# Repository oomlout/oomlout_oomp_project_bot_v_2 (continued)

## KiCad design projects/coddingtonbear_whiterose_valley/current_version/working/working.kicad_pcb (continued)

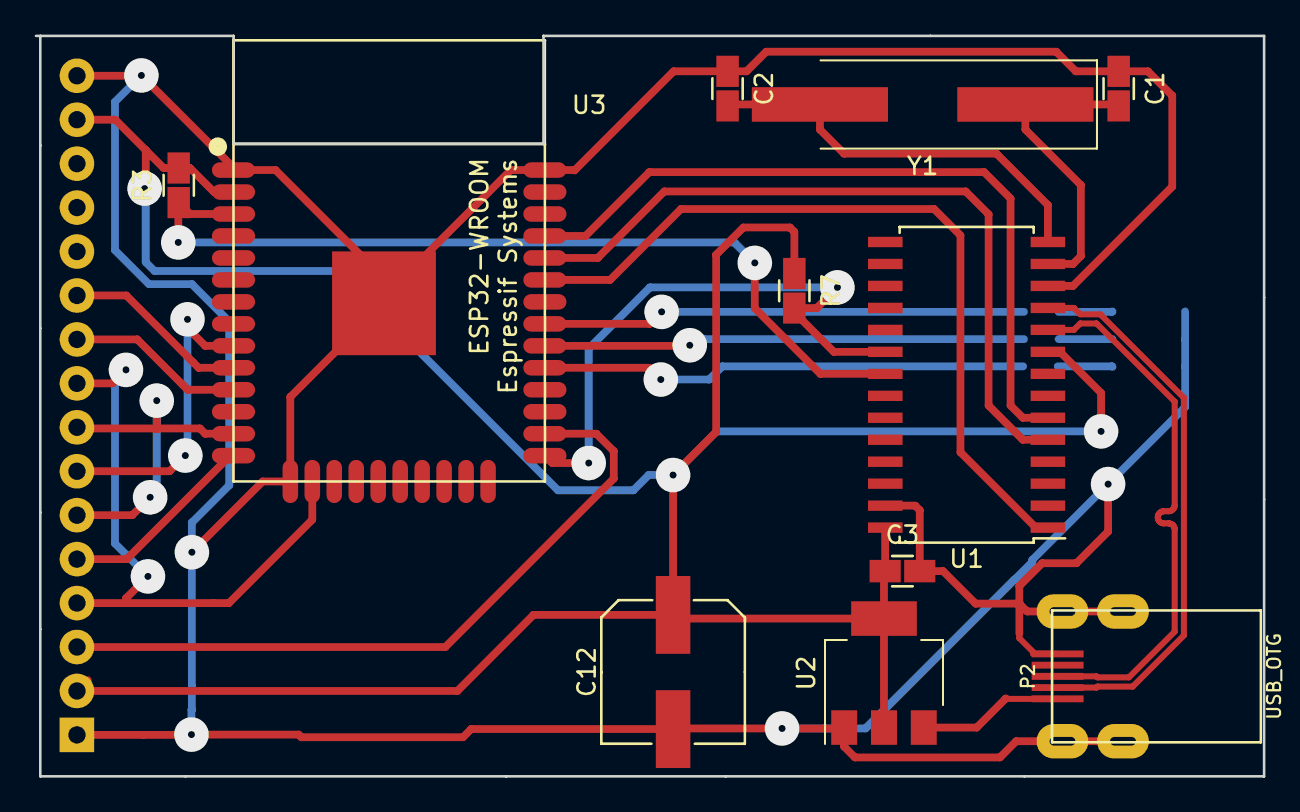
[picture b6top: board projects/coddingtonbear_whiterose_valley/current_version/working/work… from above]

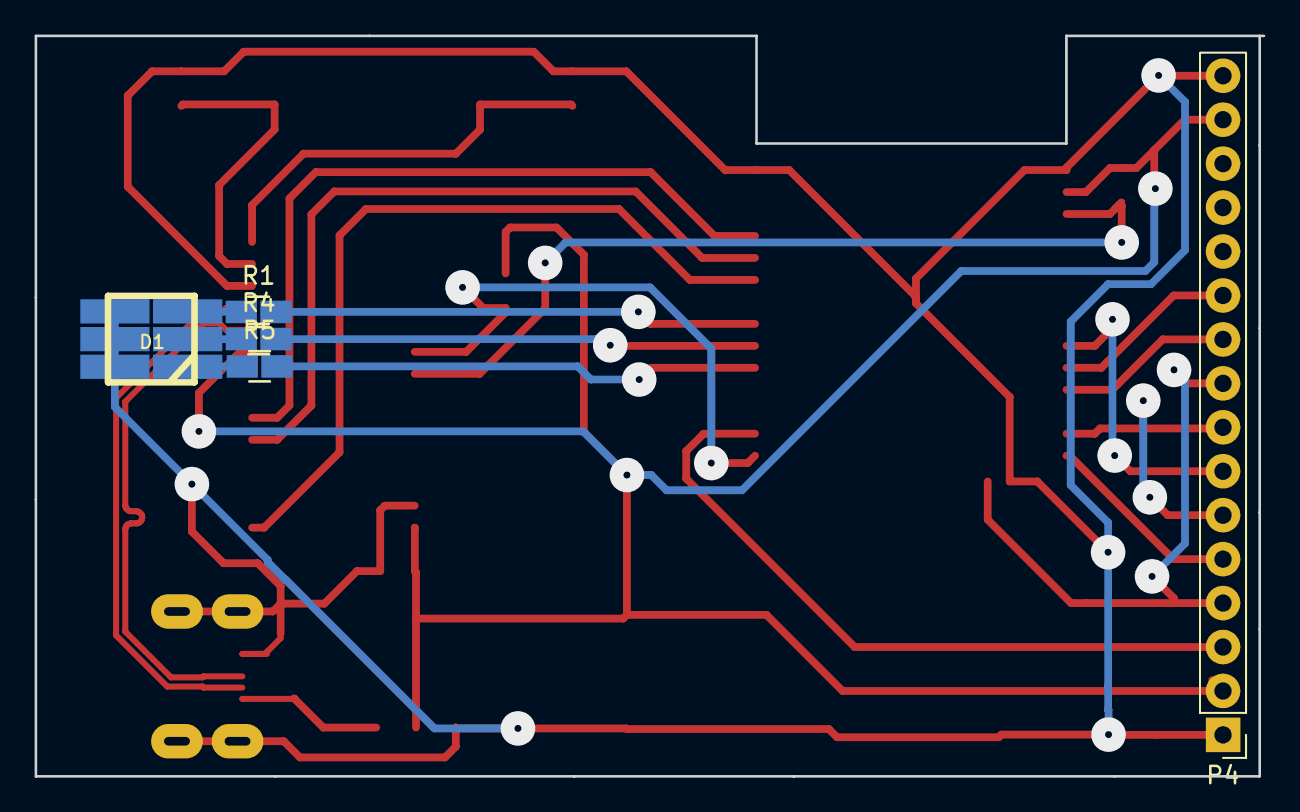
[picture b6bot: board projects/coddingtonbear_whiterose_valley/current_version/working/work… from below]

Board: 2 copper layers, 71.0 x 42.8 mm, 16 parts (5 on the bottom side), 25 nets.

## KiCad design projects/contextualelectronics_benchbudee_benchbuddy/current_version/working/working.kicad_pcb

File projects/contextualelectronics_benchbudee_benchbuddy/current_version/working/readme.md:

# benchbudee
 
## summary 
* id: contextualelectronics_benchbudee_benchbuddy
* user: contextualelectronics
* name: benchbudee
* board: benchbuddy
* repo: https://github.com/ContextualElectronics/BenchBudEE
* src_file_repo_kicad_pcb: BenchBuddy.kicad_pcb
* src_file_repo_kicad_pcb_link: https://github.com/ContextualElectronics/BenchBudEE/tree/master/BenchBuddy.kicad_pcb

* src_file_repo_sch: 
* src_file_repo_sch_link: https://github.com/ContextualElectronics/BenchBudEE/tree/master/
* full details link: https://github.com/oomlout/oomlout_oomp_project_bot_v_2/tree/main/projects/contextualelectronics_benchbudee_benchbuddy/current_version/working  

## schematic  
  
[schematic (pdf)](working_schematic.pdf) 

## pcb  

[board (pdf)](working.pdf)  

## working_bom
| Id | Designator | Footprint | Quantity | Designation | Supplier and ref |  | None | 
| --- | --- | --- | --- | --- | --- | --- | --- | 
| 1 | D2,D4 | SMA | 2 | B130-13-F |  |  | [''] | 
| 2 | R5,R3,R48,R49,R62,R63,R6,R58,R61 | SM0805 | 9 | 0 |  |  | [''] | 
| 3 | R2 | SM0805 | 1 | 200 |  |  | [''] | 
| 4 | U1 | 4-SMD | 1 | LTV-816S |  |  | [''] | 
| 5 | U2 | SSOP20 | 1 | MCP3901 |  |  | [''] | 
| 6 | U4 | SO14N | 1 | OPA4170 |  |  | [''] | 
| 7 | P2 | pin_array_3x2 | 1 | CONN_3X2 |  |  | [''] | 
| 8 | P4 | 12pinTB | 1 | 12 Pin Terminal Block |  |  | [''] | 
| 9 | U5 | SO8N | 1 | MCP4801 |  |  | [''] | 
| 10 | R16 | SM1206-NO | 1 | R |  |  | [''] | 
| 11 | R15,R14,R56,R44,R45,R13,R12,R43,R52,R53,R54,R25,R24,R23,R22,R55,R11,R26,R57 | SM0805 | 19 | R |  |  | [''] | 
| 12 | Q3,Q4 | DPAK2-BB | 2 | AOD476 |  |  | [''] | 
| 13 | L3,L2,L1 | SM1210L | 3 | CM322522-220KL |  |  | [''] | 
| 14 | C3,C4,C2 | SM1206 | 3 | C |  |  | [''] | 
| 15 | SW1 | BB_switch | 1 | Power Switch |  |  | [''] | 
| 16 | R28,R40,R42,R29,R27,R34,R30,R31,R33,R32,R37,R47,R51,R50,R35,R36,R38,R39,R41,R46 | SM0805-SB2 | 20 | R |  |  | [''] | 
| 17 | R18,R21 | SM0805 | 2 | 715 |  |  | [''] | 
| 18 | R20,R19 | EVUE3K | 2 | 5K |  |  | [''] | 
| 19 | U7 | SOT23_6 | 1 | AP5726 |  |  | [''] | 
| 20 | D5 | SOD-323 | 1 | B0540WS-7 |  |  | [''] | 
| 21 | L4 | NR4012 | 1 | 22u |  |  | [''] | 
| 22 | K1 | TE-SPDT | 1 | 1461069-5 |  |  | [''] | 
| 23 | U11,U9 | TO220_BB | 2 | LM317T |  |  | [''] | 
| 24 | U8,U6 | TO220_BB | 2 | LM337T |  |  | [''] | 
| 25 | JP1,JP2,JP3,JP4 | GND_POINT_2 | 4 | JUMPER |  |  | [''] | 
| 26 | 3 mm,3 mm,3 mm,3 mm | 3mm-NPTH | 4 | VAL** |  |  | [''] | 
| 27 | ARD1 | Arduino | 1 | ARDUINOPINS |  |  | [''] | 
| 28 | P3 | SM0805 | 1 | CONN_2 |  |  | [''] | 
| 29 | C31,C32,C7,C8,C10,C9,C11,C1,C13,C12,C17,C22,C23,C16,C15,C14,C21,C20,C19,C18,C24,C25,C30,C33 | SM0805 | 24 | C |  |  | [''] | 
| 30 | P1 | ATX_Header | 1 | 24 Pin MiniFit JR |  |  | [''] | 
| 31 | D1 | LED-0603-2 | 1 | LG Q971-KN-1 |  |  | [''] | 
| 32 | G*** | OSHW_CU | 1 | OSHW_CU |  |  | [''] | 
| 33 | G*** | OSHW_SM | 1 | OSHW_SM |  |  | [''] | 
| 34 | P7,P6 | V8508H | 2 | CONN_1 |  |  | [''] | 
| 35 | P5 | 3pinTB | 1 | 3 Pin TB |  |  | [''] | 
| 36 | TP3 | TestPointTH | 1 | CH0 |  |  | [''] | 
| 37 | TP2 | TestPointTH | 1 | CH1 |  |  | [''] | 
| 38 | TP1 | TestPointTH | 1 | 5V |  |  | [''] | 
| 39 | TP5 | TestPointTH | 1 | RELAY_LOW |  |  | [''] | 
| 40 | TP4 | TestPointTH | 1 | +12P |  |  | [''] | 
| 41 | TP9 | TestPointTH | 1 | GND_PWR |  |  | [''] | 
| 42 | TP10 | TestPointTH | 1 | DAC_OUT |  |  | [''] | 
| 43 | R60,R59 | SM0805 | 2 | 1K |  |  | [''] | 
| 44 | K3,K2 | PIN_ARRAY_3X1 | 2 | CONN_3 |  |  | [''] | 
| 45 | TP6 | TestPointTH | 1 | AGND |  |  | [''] | 
| 46 | G*** | CE-LOGO | 1 | CE-LOGO |  |  | [''] | 
| 47 | Q1 | SOT23EBC | 1 | 2N3904 |  |  | [''] | 
| 48 | R1 | SM0805 | 1 | 500 |  |  | [''] | 
| 49 | R4 | SM0805 | 1 | 100 |  |  | [''] | 
| 50 | U3 | SOT353 | 1 | LMT84 |  |  | [''] | 
| 51 | R9,R8,R7,R10 | SM1206 | 4 | R |  |  | [''] | 
| 52 | Q2 | SOT23GDS | 1 | DMN65D8L-7 |  |  | [''] | 
| 53 | TH5,TH1,TH2,TH3,TH4 | SM1812 | 5 | MINISMDC050F-2 |  |  | [''] | 
| 54 | D10,D8,D9,D12,D7,D3,D11,D6 | SOT23-DIODE | 8 | MMBD914-7-F |  |  | [''] | 
| 55 | C5,C6 | SM0805 | 2 | 1U |  |  | [''] | 
| 56 | R17 | SM0805 | 1 | 15 |  |  | [''] | 
| 57 | L5 | SM0805 | 1 | INDUCTOR |  |  | [''] | 
| 58 | C29,C28,C27,C26 | SM1210 | 4 | C |  |  | [''] | 

## bom_schematic
no data

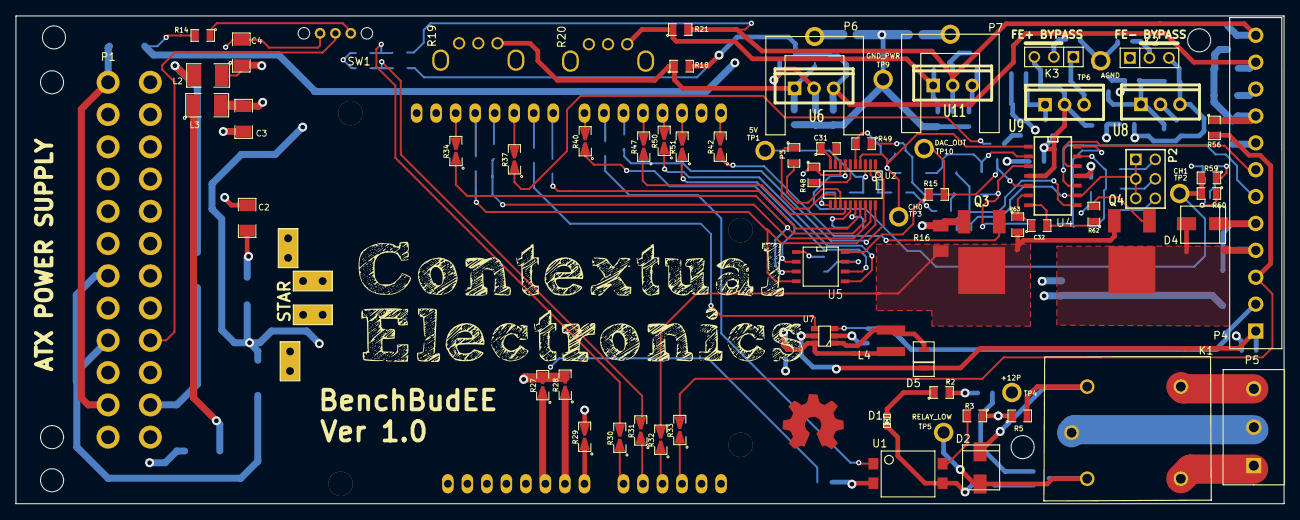
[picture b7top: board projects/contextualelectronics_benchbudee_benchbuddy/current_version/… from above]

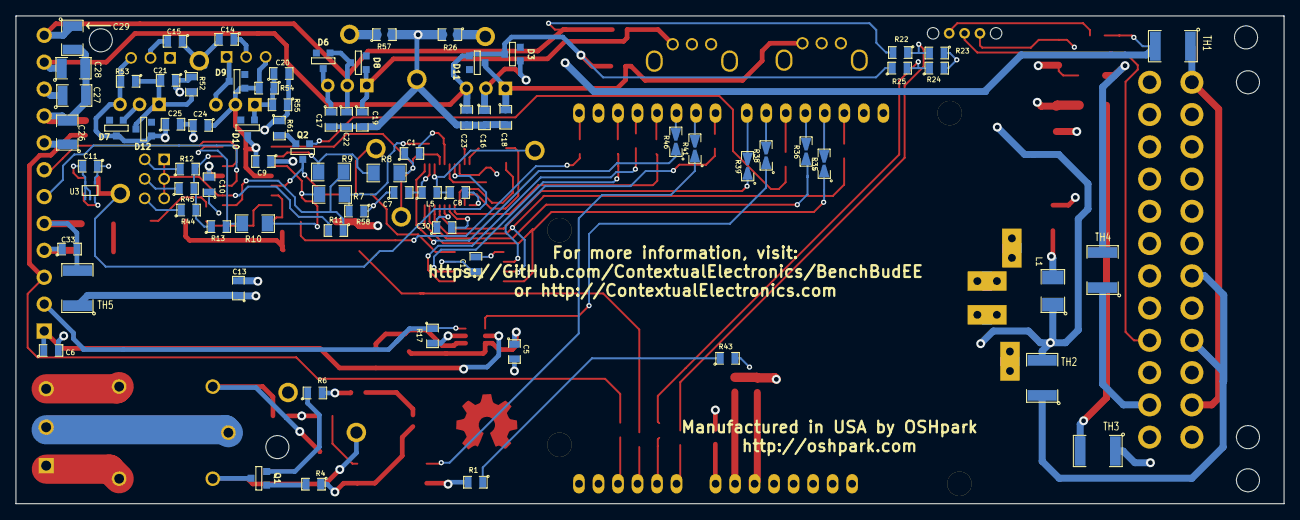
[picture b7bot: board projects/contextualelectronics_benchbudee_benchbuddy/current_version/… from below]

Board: 4 copper layers, 165.1 x 63.5 mm, 160 parts (78 on the bottom side), 114 nets.

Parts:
3 mm, 3 mm#2, 3 mm#3, 3 mm#4: VAL**; 3mm-NPTH
ARD1: ARDUINOPINS; Arduino
C1, C7, C8, C9, C10, C11, C12, C13, C14, C15, C16, C17, C18, C19, C20, C21, C22, C23, C24, C25, C30, C31, C32, C33: C; SM0805
C2, C3, C4: C; SM1206
C5, C6: 1U; SM0805
C26, C27, C28, C29: C; SM1210
D1: LG Q971-KN-1; LED-0603-2
D2, D4: B130-13-F; SMA
D3, D6, D7, D8, D9, D10, D11, D12: MMBD914-7-F; SOT23-DIODE
D5: B0540WS-7; SOD-323
JP1, JP2, JP3, JP4: JUMPER; GND_POINT_2
K1: 1461069-5; TE-SPDT
K2, K3: CONN_3; PIN_ARRAY_3X1
L1, L2, L3: CM322522-220KL; SM1210L
L4: 22u; NR4012
L5: INDUCTOR; SM0805
P1: 24 Pin MiniFit JR; ATX_Header
P2: CONN_3X2; pin_array_3x2
P3: CONN_2; SM0805
P4: 12 Pin Terminal Block; 12pinTB
P5: 3 Pin TB; 3pinTB
P6, P7: CONN_1; V8508H
Q1: 2N3904; SOT23EBC
Q2: DMN65D8L-7; SOT23GDS
Q3, Q4: AOD476; DPAK2-BB
R1: 500; SM0805
R2: 200; SM0805
R3, R5, R6, R48, R49, R58, R61, R62, R63: 0; SM0805
R4: 100; SM0805
R7, R8, R9, R10: R; SM1206
R11, R12, R13, R14, R15, R22, R23, R24, R25, R26, R43, R44, R45, R52, R53, R54, R55, R56, R57: R; SM0805
R16: R; SM1206-NO
R17: 15; SM0805
R18, R21: 715; SM0805
R19, R20: 5K; EVUE3K
R27, R28, R29, R30, R31, R32, R33, R34, R35, R36, R37, R38, R39, R40, R41, R42, R46, R47, R50, R51: R; SM0805-SB2
R59, R60: 1K; SM0805
SW1: Power Switch; BB_switch
TH1, TH2, TH3, TH4, TH5: MINISMDC050F-2; SM1812
TP1: 5V; TestPointTH
TP2: CH1; TestPointTH
TP3: CH0; TestPointTH
TP4: +12P; TestPointTH
TP5: RELAY_LOW; TestPointTH
TP6: AGND; TestPointTH
TP9: GND_PWR; TestPointTH
TP10: DAC_OUT; TestPointTH
U1: LTV-816S; 4-SMD
U2: MCP3901; SSOP20
U3: LMT84; SOT353
U4: OPA4170; SO14N
U5: MCP4801; SO8N
U6, U8: LM337T; TO220_BB
U7: AP5726; SOT23_6
U9, U11: LM317T; TO220_BB

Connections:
+3.3V: C27.1, P4.10, R14.2, TH1.2
+5P: C5.1, C26.1, L1.1, L4.1, P4.8, TH2.2, U7.6
+5V: C2.1, C8.1, C11.1, C12.2, L1.2, L5.2, TP1.1, U2.3, U3.4, U5.1
+12C: C13.1, P1.10, TH3.1, TH5.1
+12P: L3.1, R3.1, R5.1, R29.2, TH3.2, TP4.1
+12V: C3.1, C14.1, C17.1, D6.2, K3.2, L3.2, U11.3
-12P: L2.2, TH4.2
-12V: C4.2, C15.2, C16.1, D3.1, K2.2, L2.1, U6.2
/Arduino/CURR_MEAS: Q3.2, Q4.3, R16.1, R32.2, R63.2
/Arduino/FAN_MODE: Q3.1, R42.1
/Arduino/FAN_PWM: Q2.G, R37.1
/Arduino/LED_EN_PWM: R38.1, U7.4
/Arduino/MISO: R36.1, U2.19
/Arduino/MOSI: R35.1, U2.20, U5.4
/Arduino/RELAY+: R41.1, U1.1
/Arduino/RELAY-: R1.1, R43.1
/Arduino/SCLK: R34.1, U2.18, U5.3
/Arduino/V+_ADJ_MON: R22.1, R23.2, R30.2
/Arduino/V-_ADJ_MON: R24.1, R25.2, R31.2
/Arduino/~ADC_CS: R39.1, U2.17
/Arduino/~DR: R47.1, U2.14
/Arduino/~LDAC: R50.1, U5.5
/Arduino/~RESET: R46.1, U2.1
/Arduino/~SHDN: R51.1, U5.6
/Fan/CS_N: R40.1, U5.2
/Fan/FAN_OUT+: C33.2, D4.2, P4.5, TH5.2
/Fan/FAN_OUT-: C33.1, D4.1, P4.4, Q4.2
/Fan/TACH_IN: P4.3, R33.2, R56.2
/LED_Driver/LED_STRING+: C6.1, D5.2, P4.1, U7.5
/LED_Driver/LED_STRING-: P4.2, R17.1, U7.3
/PowerAdjustmentMonitor/V+_ADJ: C22.1, C29.1, D6.1, D8.2, P4.12, R21.2, R22.2, U11.2
/PowerAdjustmentMonitor/V-_ADJ: C23.1, C28.1, D3.2, D11.1, P4.11, R18.2, R25.1, U6.3
/Relay/RELAY_COM: K1.1, P5.2
/Relay/RELAY_NC: K1.3, P5.3
/Relay/RELAY_NO: K1.4, P5.1
/Thermocouple/CH0+: C1.1, R8.1, TP3.1, U2.4, U4.1
/Thermocouple/CH0-: C1.2, R49.2, U2.5
/Thermocouple/CH1+: R59.2, R60.2, TP2.1, U2.7
/Thermocouple/CH1-: R48.2, U2.6
/Thermocouple/TC IN +: P4.7, U4.12
/Thermocouple/TC IN -: P4.6, U4.10
AGND: C7.1, C8.2, C9.1, C10.1, C11.2, C12.1, C13.2, C14.2, C15.1, C20.2, C21.1, C24.2, C25.2, JP1.2, Q3.3, R16.2, R48.1, R52.1, R55.1, R58.1, R59.1, R61.1, TP6.1, U2.8, U2.11, U3.1, U3.2, U3.5, U5.7
FE_V+: C9.2, C24.1, D9.1, D10.2, K3.3, R54.2, U4.4, U9.2
FE_V-: C10.2, C25.1, D7.2, D12.1, K2.3, R53.2, U4.11, U8.3
GND: C2.2, C3.2, C4.1, JP1.1, JP2.1, JP3.1, JP4.1, P1.3, P1.5, R27.2, R28.2, R43.2, SW1.3
GND_LED: C5.2, C6.2, JP3.2, R17.2, U7.2
GND_PWR: C16.2, C17.2, C18.2, C19.2, C22.2, C23.2, C26.2, C27.2, C28.2, C29.2, JP2.2, P4.9, R19.2, R20.2, R23.1, R24.2, R26.2, R56.1, R57.2, TP9.1
GND_RELAY: JP4.2, R2.2, R6.2
unnamed: ARD1.2, R27.1
unnamed: ARD1.20, R38.2
unnamed: ARD1.11, R42.2
unnamed: ARD1.4, R29.1
unnamed: ARD1.3, R28.1
unnamed: ARD1.16, R46.2
unnamed: ARD1.15, R47.2
unnamed: ARD1.14, R50.2
unnamed: ARD1.13, R51.2
unnamed: ARD1.17, R41.2
unnamed: ARD1.18, R40.2
unnamed: ARD1.7, R32.1
unnamed: ARD1.8, R33.1
unnamed: ARD1.6, R31.1
unnamed: ARD1.5, R30.1
unnamed: ARD1.21, R37.2
unnamed: ARD1.19, R39.2
unnamed: ARD1.24, R34.2
unnamed: ARD1.23, R35.2
unnamed: ARD1.22, R36.2
unnamed: R60.1, U3.3
unnamed: C30.2, U2.15
unnamed: C30.1, U2.16
unnamed: C31.2, U2.9
unnamed: C31.1, U2.10
unnamed: P3.1, U2.12
unnamed: P2.2, R12.1
unnamed: P2.4, R45.1
unnamed: P2.6, R44.1
unnamed: R8.2, R9.1, U4.2
unnamed: R7.2, R10.1, U4.3
unnamed: R9.2, R11.1, U4.8
unnamed: P2.1, P2.3, P2.5, R11.2, U4.9
unnamed: R12.2, R13.1, R44.2, R45.2, U4.13
unnamed: R10.2, R13.2, U4.14
unnamed: P3.2, U2.13
unnamed: R7.1, R49.1, R58.2
unnamed: C7.2, L5.1, U2.2
unnamed: D1.2, R2.1
unnamed: Q1.1, R6.1
unnamed: Q1.2, R4.2
unnamed: R1.2, U1.2
unnamed: D2.1, K1.5, Q1.3, TP5.1
unnamed: D2.2, K1.2, R5.2
unnamed: D1.1, R4.1, U1.3
unnamed: R3.2, U1.4
unnamed: P1.14, TH4.1
unnamed: R14.1, SW1.1
unnamed: P1.16, SW1.2
unnamed: P1.2, P1.12, TH1.1
unnamed: P1.4, P1.6, TH2.1
unnamed: D5.1, L4.2, U7.1
unnamed: Q2.S, R61.2
unnamed: Q4.1, R62.2
unnamed: C32.1, R63.1, U4.6
unnamed: C32.2, R62.1, U4.7
unnamed: R15.1, U5.8
unnamed: Q2.D, R15.2, TP10.1, U4.5
unnamed: C19.1, D8.1, R20.1, R21.1, U11.1
unnamed: C20.1, D10.1, R54.1, R55.2, U9.1
unnamed: C21.2, D12.2, R52.2, R53.1, U8.1
unnamed: P6.1, R26.1
unnamed: P7.1, R57.1
unnamed: C18.1, D11.2, R18.1, R19.1, U6.1
unnamed: D9.2, K3.1, U9.3
unnamed: D7.1, K2.1, U8.2
